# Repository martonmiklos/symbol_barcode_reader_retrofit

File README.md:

# Replacement PCB for the Symbol LS4208 barcode reader

Drawn in EAGLE

For moare details see:

https://hackaday.io/project/166845-symbol-ls4208-barcode-reader-retrofit

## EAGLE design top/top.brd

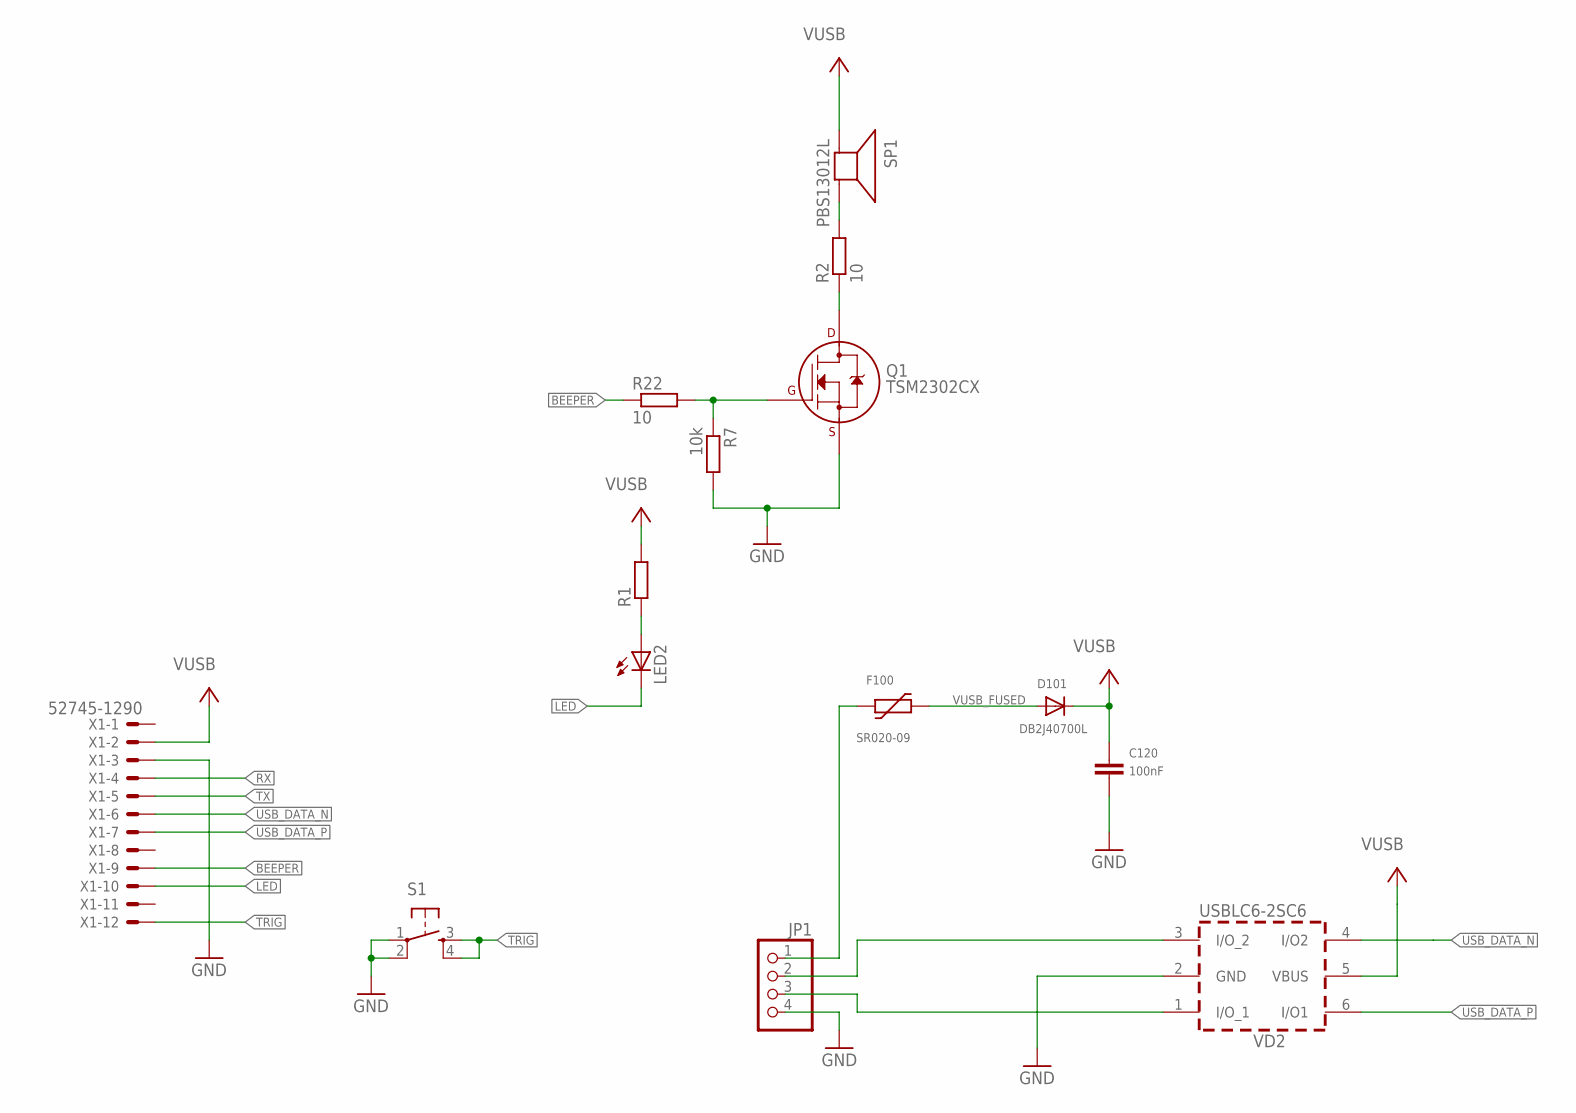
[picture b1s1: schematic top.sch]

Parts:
C120: 100nF; C0603K
D101: DB2J40700L; SOD-323F
F100: SR020-09; PTC0805
JP1: PINHD-1X4; 1X04
LED2: LEDCHIP-LED0805; CHIP-LED0805
Q1: TSM2302CX; SOT-23
R1: R-EU_R0603; R0603
R2, R22: 10; R0603
R7: 10k; R0603
S1: TAC_SWITCHSMD; TACTILE_SWITCH_SMD
SP1: PBS13012L; AL60P
VD2: USBLC6-2SC6; SOT-23-6L
X1: 52745-1290

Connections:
BEEPER: R22.1, X1.9
BEEPER_FET_DRAIN: Q1.3 (D), R2.1
BEEPER_R: R2.2, SP1.2 (-)
BUZZER_BEFORERES: Q1.1 (G), R7.1, R22.2
GND: C120.2, JP1.4, Q1.2 (S), R7.2, S1.1, S1.2, VD2.2 (GND), X1.3
LED: LED2.C, X1.10
LED_R: LED2.A, R1.1
RX: X1.4
TRIG: S1.3, S1.4, X1.12
TX: X1.5
USB_DATA_N: VD2.4 (I/O2), X1.6
USB_DATA_P: VD2.6 (I/O1), X1.7
USB_DATA_UNPROT_N: JP1.2, VD2.3 (I/O_2)
USB_DATA_UNPROT_P: JP1.3, VD2.1 (I/O_1)
VUSB: C120.1, D101.C, R1.2, SP1.1 (+), VD2.5 (VBUS), X1.2
VUSB_FUSED: D101.A, F100.2
VUSB_UNPROT: F100.1, JP1.1

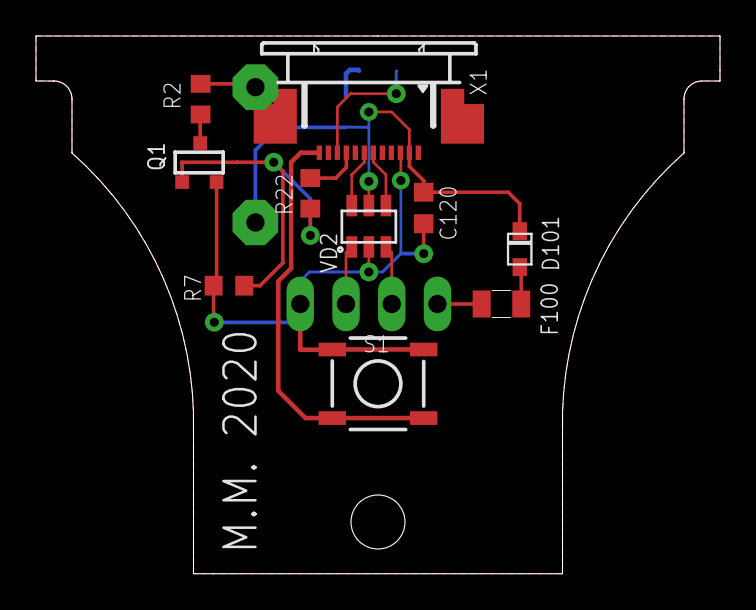
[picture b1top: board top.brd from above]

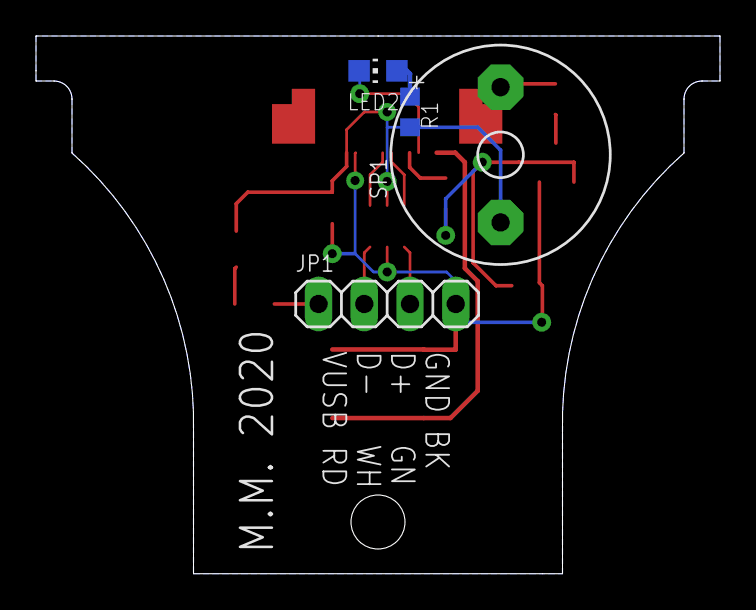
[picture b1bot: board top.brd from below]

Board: 2 copper layers, 38.0 x 29.9 mm, 14 parts (4 on the bottom side), 15 nets.

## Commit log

2019-07-30 Add initial files
2021-06-16 Added silkscreen texts

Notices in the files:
parts and their libraries:
SparkFun: Licensing: CC v3.0 Share-Alike You are welcome to use this library for commercial purposes.
